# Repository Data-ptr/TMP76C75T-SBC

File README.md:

# TMP76C75T SBC
 (My first PCB) My attempt at a SBC for the MH6111/TMP76C75T microprocessor
 
Front:

Back:

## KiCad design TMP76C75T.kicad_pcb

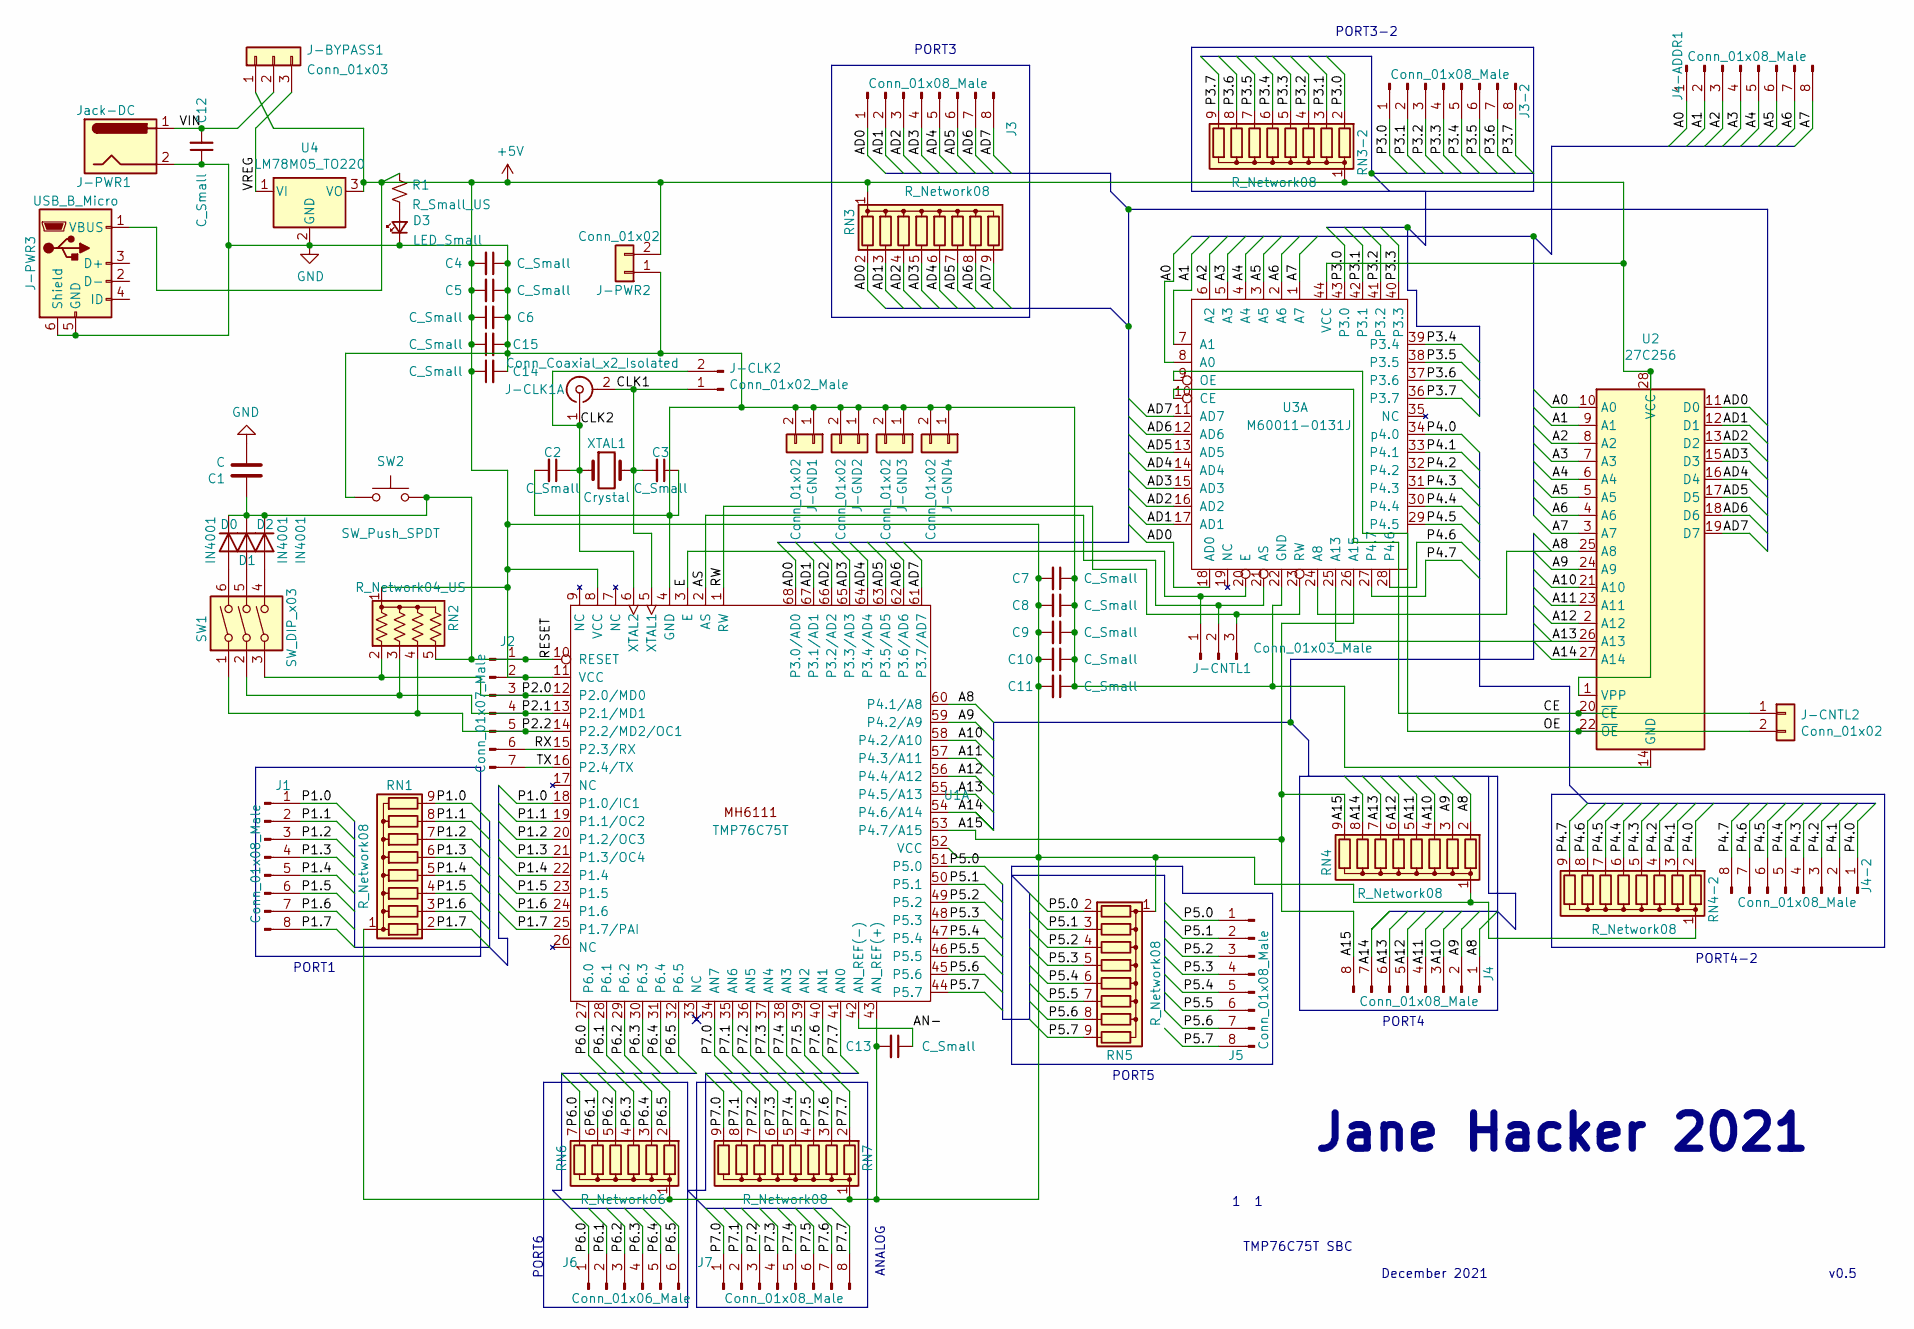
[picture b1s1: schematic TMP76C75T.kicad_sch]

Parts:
C1: C; CP_Radial_D5.0mm_P2.50mm
C2, C3, C4, C7, C8, C9, C10, C11, C12, C13, C14: C_Small; C_1206_3216Metric
C5, C15: C_Small; C_2816_7142Metric
C6: C_Small; CP_Radial_D5.0mm_P2.50mm
D0, D1, D2: IN4001; D_A-405_P10.16mm_Horizontal
D3: LED_Small; LED_D3.0mm
J1, J3, J3-2, J4, J4-2, J4-ADDR1, J5, J7: Conn_01x08_Male; PinHeader_1x08_P2.54mm_Vertical
J2: Conn_01x07_Male; PinHeader_1x07_P2.54mm_Vertical
J6: Conn_01x06_Male; PinHeader_1x06_P2.54mm_Vertical
J-BYPASS1: Conn_01x03; PinHeader_1x03_P2.54mm_Vertical
J-CLK1: Conn_Coaxial_x2_Isolated; SMA_Amphenol_901-144_Vertical
J-CLK2: Conn_01x02_Male; PinHeader_1x02_P2.54mm_Vertical
J-CNTL1: Conn_01x03_Male; PinHeader_1x03_P2.54mm_Vertical
J-CNTL2: Conn_01x02; PinHeader_1x02_P2.54mm_Vertical
J-GND1, J-GND2, J-GND3, J-GND4: Conn_01x02; PinHeader_1x02_P2.54mm_Vertical
J-PWR1: Jack-DC; BarrelJack_CUI_PJ-063AH_Horizontal
J-PWR2: Conn_01x02; PinHeader_1x02_P2.54mm_Vertical
J-PWR3: USB_B_Micro; USB_Micro-B_Wuerth_629105150521
R1: R_Small_US; R_Axial_DIN0207_L6.3mm_D2.5mm_P2.54mm_Vertical
RN1, RN3, RN3-2, RN4, RN4-2, RN5, RN7: R_Network08; R_Array_SIP9
RN2: R_Network04_US; R_Array_SIP5
RN6: R_Network06; R_Array_SIP7
SW1: SW_DIP_x03; SW_DIP_SPSTx03_Slide_9.78x9.8mm_W7.62mm_P2.54mm
SW2: SW_Push_SPDT; SW_PUSH_6mm_H5mm
U1: TMP76C75T; PLCC-68_THT-Socket
U2: 27C256; DIP_Socket-28_W11.9_W12.7_W15.24_W17.78_W18.5_3M_228-1277-0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
U3: M60011-0131J; PLCC-44_THT-Socket
U4: LM78M05_TO220; TO-220-3_Vertical
XTAL1: Crystal; Crystal_HC18-U_Vertical

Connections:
+5V: C4.2, C5.2, C6.1, C7.2, C8.2, C9.2, C10.2, C11.2, C13.2, C14.1, C15.1, J2.2, J-BYPASS1.1, J-PWR2.2, J-PWR3.1 (VBUS), R1.1, RN1.1 (common), RN2.1 (common), RN3.1 (common), RN3-2.1 (common), RN4.1 (common), RN4-2.1 (common), RN5.1 (common), RN6.1 (common), RN7.1 (common), U1.8 (VCC), U1.11 (VCC), U1.43 (AN_REF(+)), U1.52 (VCC), U2.1 (VPP), U2.28 (VCC), U3.44 (VCC), U4.3 (VO)
/A0: J4-ADDR1.1, U2.10 (A0), U3.8 (A0)
/A1: J4-ADDR1.2, U2.9 (A1), U3.7 (A1)
/A2: J4-ADDR1.3, U2.8 (A2), U3.6 (A2)
/A3: J4-ADDR1.4, U2.7 (A3), U3.5 (A3)
/A4: J4-ADDR1.5, U2.6 (A4), U3.4 (A4)
/A5: J4-ADDR1.6, U2.5 (A5), U3.3 (A5)
/A6: J4-ADDR1.7, U2.4 (A6), U3.2 (A6)
/A7: J4-ADDR1.8, U2.3 (A7), U3.1 (A7)
/A8: J4.1, RN4.2 (R1), U1.60 (P4.1/A8), U2.25 (A8), U3.24 (A8)
/A9: J4.2, RN4.3 (R2), U1.59 (P4.2/A9), U2.24 (A9)
/A10: J4.3, RN4.4 (R3), U1.58 (P4.2/A10), U2.21 (A10)
/A11: J4.4, RN4.5 (R4), U1.57 (P4.3/A11), U2.23 (A11)
/A12: J4.5, RN4.6 (R5), U1.56 (P4.4/A12), U2.2 (A12)
/A13: J4.6, RN4.7 (R6), U1.55 (P4.5/A13), U2.26 (A13), U3.25 (A13)
/A14: J4.7, RN4.8 (R7), U1.54 (P4.6/A14), U2.27 (A14)
/A15: J4.8, RN4.9 (R8), U1.53 (P4.7/A15), U3.26 (A15)
/AD0: J3.1, RN3.2 (R1), U1.68 (P3.0/AD0), U2.11 (D0), U3.18 (AD0)
/AD1: J3.2, RN3.3 (R2), U1.67 (P3.1/AD1), U2.12 (D1), U3.17 (AD1)
/AD2: J3.3, RN3.4 (R3), U1.66 (P3.2/AD2), U2.13 (D2), U3.16 (AD2)
/AD3: J3.4, RN3.5 (R4), U1.65 (P3.3/AD3), U2.15 (D3), U3.15 (AD3)
/AD4: J3.5, RN3.6 (R5), U1.64 (P3.4/AD4), U2.16 (D4), U3.14 (AD4)
/AD5: J3.6, RN3.7 (R6), U1.63 (P3.5/AD5), U2.17 (D5), U3.13 (AD5)
/AD6: J3.7, RN3.8 (R7), U1.62 (P3.6/AD6), U2.18 (D6), U3.12 (AD6)
/AD7: J3.8, RN3.9 (R8), U1.61 (P3.7/AD7), U2.19 (D7), U3.11 (AD7)
/AN-: C13.1, U1.42 (AN_REF(-))
/AS: J-CNTL1.2, U1.2 (AS), U3.21 (AS)
/CE: J-CNTL2.1, U2.20 (~CE), U3.10 (CE)
/CLK1: C3.2, J-CLK1.2 (Ext1), J-CLK2.1, U1.5 (XTAL1), XTAL1.2
/CLK2: C2.1, J-CLK1.1 (In1), J-CLK2.2, U1.6 (XTAL2), XTAL1.1
/E: J-CNTL1.1, U1.3 (E), U3.20 (E)
/OE: J-CNTL2.2, U2.22 (~OE), U3.9 (OE)
/P1.0: J1.1, RN1.9 (R8), U1.18 (P1.0/IC1)
/P1.1: J1.2, RN1.8 (R7), U1.19 (P1.1/OC2)
/P1.2: J1.3, RN1.7 (R6), U1.20 (P1.2/OC3)
/P1.3: J1.4, RN1.6 (R5), U1.21 (P1.3/OC4)
/P1.4: J1.5, RN1.5 (R4), U1.22 (P1.4)
/P1.5: J1.6, RN1.4 (R3), U1.23 (P1.5)
/P1.6: J1.7, RN1.3 (R2), U1.24 (P1.6)
/P1.7: J1.8, RN1.2 (R1), U1.25 (P1.7/PAI)
/P2.0: J2.3, RN2.2 (R1), SW1.3, U1.12 (P2.0/MD0)
/P2.1: J2.4, RN2.3 (R2), SW1.2, U1.13 (P2.1/MD1)
/P2.2: J2.5, RN2.4 (R3), SW1.1, U1.14 (P2.2/MD2/OC1)
/P3.0: J3-2.1, RN3-2.2 (R1), U3.43 (P3.0)
/P3.1: J3-2.2, RN3-2.3 (R2), U3.42 (P3.1)
/P3.2: J3-2.3, RN3-2.4 (R3), U3.41 (P3.2)
/P3.3: J3-2.4, RN3-2.5 (R4), U3.40 (P3.3)
/P3.4: J3-2.5, RN3-2.6 (R5), U3.39 (P3.4)
/P3.5: J3-2.6, RN3-2.7 (R6), U3.38 (P3.5)
/P3.6: J3-2.7, RN3-2.8 (R7), U3.37 (P3.6)
/P3.7: J3-2.8, RN3-2.9 (R8), U3.36 (P3.7)
/P4.0: J4-2.1, RN4-2.2 (R1), U3.34 (p4.0)
/P4.1: J4-2.2, RN4-2.3 (R2), U3.33 (P4.1)
/P4.2: J4-2.3, RN4-2.4 (R3), U3.32 (P4.2)
/P4.3: J4-2.4, RN4-2.5 (R4), U3.31 (P4.3)
/P4.4: J4-2.5, RN4-2.6 (R5), U3.30 (P4.4)
/P4.5: J4-2.6, RN4-2.7 (R6), U3.29 (P4.5)
/P4.6: J4-2.7, RN4-2.8 (R7), U3.28 (P4.6)
/P4.7: J4-2.8, RN4-2.9 (R8), U3.27 (P4.7)
/P5.0: J5.1, RN5.2 (R1), U1.51 (P5.0)
/P5.1: J5.2, RN5.3 (R2), U1.50 (P5.1)
/P5.2: J5.3, RN5.4 (R3), U1.49 (P5.2)
/P5.3: J5.4, RN5.5 (R4), U1.48 (P5.3)
/P5.4: J5.5, RN5.6 (R5), U1.47 (P5.4)
/P5.5: J5.6, RN5.7 (R6), U1.46 (P5.5)
/P5.6: J5.7, RN5.8 (R7), U1.45 (P5.6)
/P5.7: J5.8, RN5.9 (R8), U1.44 (P5.7)
/P6.0: J6.1, RN6.7 (R6), U1.27 (P6.0)
/P6.1: J6.2, RN6.6 (R5), U1.28 (P6.1)
/P6.2: J6.3, RN6.5 (R4), U1.29 (P6.2)
/P6.3: J6.4, RN6.4 (R3), U1.30 (P6.3)
/P6.4: J6.5, RN6.3 (R2), U1.31 (P6.4)
/P6.5: J6.6, RN6.2 (R1), U1.32 (P6.5)
/P7.0: J7.1, RN7.9 (R8), U1.34 (AN7)
/P7.1: J7.2, RN7.8 (R7), U1.35 (AN6)
/P7.2: J7.3, RN7.7 (R6), U1.36 (AN5)
/P7.3: J7.4, RN7.6 (R5), U1.37 (AN4)
/P7.4: J7.5, RN7.5 (R4), U1.38 (AN3)
/P7.5: J7.6, RN7.4 (R3), U1.39 (AN2)
/P7.6: J7.7, RN7.3 (R2), U1.40 (AN1)
/P7.7: J7.8, RN7.2 (R1), U1.41 (AN0)
/RESET: C1.1, D0.1 (K), D1.1 (K), D2.1 (K), J2.1, RN2.5 (R4), SW2.2, U1.10 (RESET)
/RW: J-CNTL1.3, U1.1 (RW), U3.23 (RW)
/RX: J2.6, U1.15 (P2.3/RX)
/TX: J2.7, U1.16 (P2.4/TX)
/VIN: C12.2, J-BYPASS1.2, J-PWR1.1
/VREG: J-BYPASS1.3, U4.1 (VI)
GND: C1.2, C2.2, C3.1, C4.1, C5.1, C6.2, C7.1, C8.1, C9.1, C10.1, C11.1, C12.1, C14.2, C15.2, D3.1 (K), J-GND1.1, J-GND1.2, J-GND2.1, J-GND2.2, J-GND3.1, J-GND3.2, J-GND4.1, J-GND4.2, J-PWR1.2, J-PWR2.1, J-PWR3.5 (GND), J-PWR3.6 (Shield), SW2.1, U1.4 (GND), U2.14 (GND), U3.22 (GND), U4.2 (GND)
unnamed: D0.2 (A), SW1.6
unnamed: D1.2 (A), SW1.5
unnamed: D2.2 (A), SW1.4
unnamed: D3.2 (A), R1.2

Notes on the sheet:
PORT3-2
PORT6
1 1
TMP76C75T SBC
PORT3
ANALOG
PORT4
Jane Hacker 2021
PORT1
v0.5
December 2021
PORT4-2
PORT5

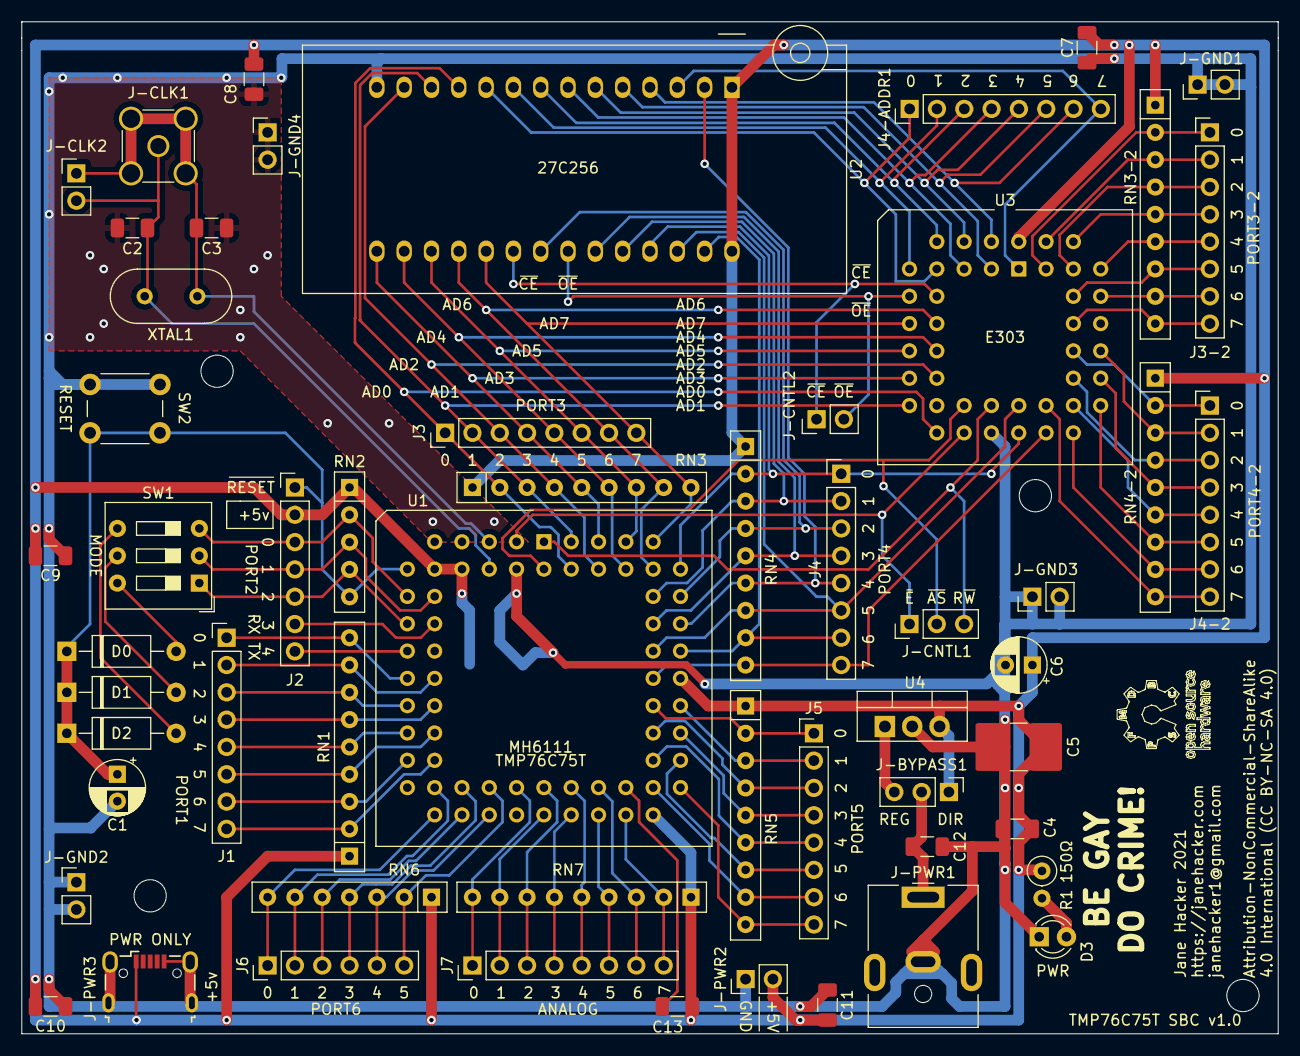
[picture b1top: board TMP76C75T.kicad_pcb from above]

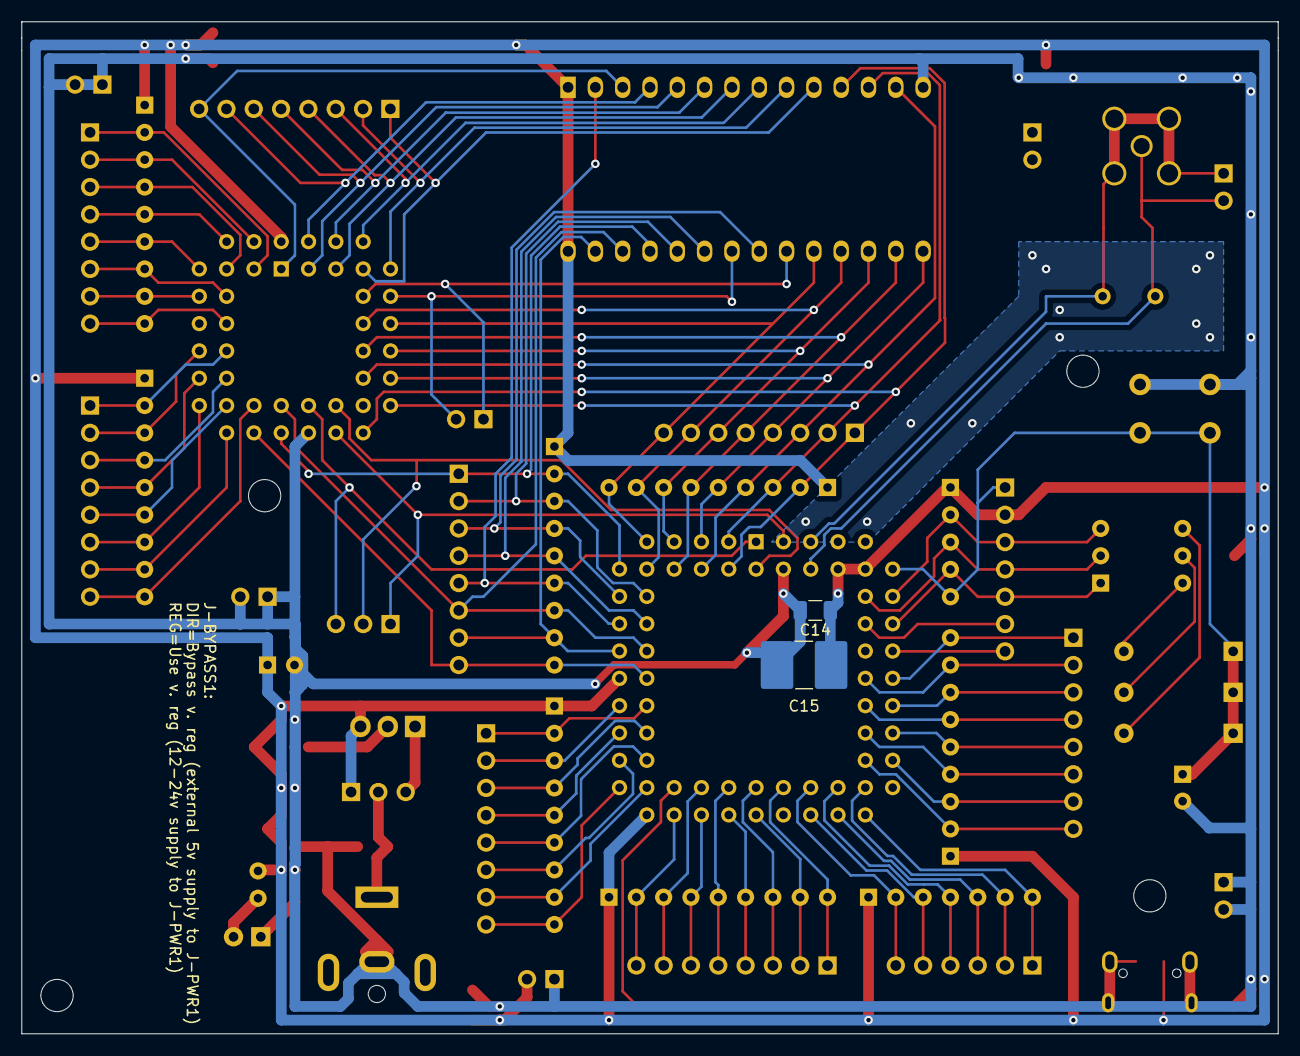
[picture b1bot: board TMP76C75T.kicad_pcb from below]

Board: 2 copper layers, 116.8 x 94.1 mm, 58 parts (2 on the bottom side), 92 nets.

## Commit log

2021-12-04 Adding design files
2021-12-04 Added via labels
2021-12-05 Small changes
2022-01-15 Fixes and nice updates
    Fixed power rails for M303, fixed reset line tied to cap, added ground headers, adde clock header
2022-02-23 v1.0 Update!
2022-03-01 Adding images
2022-03-01 Adding images to README.md

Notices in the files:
TMP76C75T.kicad_pcb:
4.0 International (CC BY-NC-SA 4.0)
